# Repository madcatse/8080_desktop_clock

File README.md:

# i8080 homebrew digital clock/weather station (fork)

## Русский

Этот репозиторий — форк проекта **"i8080 homebrew digital clock/weather station"** автора **Tronix286**: 
<https://github.com/Tronix286/i8080_clock>.

Моя цель — сделать часы более презентабельными и свести к минимуму использование SMD‑компонентов (с таким процессором использовать их «не комильфо»). Я очень благодарен автору за схему и само устройство — без этой базы не получилось бы так быстро продвинуться.

Ключевое отличие от исходного проекта: в этом форке сделан упор на внешний вид и на максимально сквозной/выводной монтаж, поэтому плата и компоновка ориентированы на более «классическое» исполнение и удобство сборки, при сохранении общей архитектуры.

### Что внутри

**Аппаратная часть**
- Плата i8080‑совместимого компьютера с тактированием, шиной, ПЗУ/ОЗУ и часами реального времени.
- Внешние устройства: TFT‑дисплей, датчики по I2C и 1‑Wire, кнопки.

**Проект в KiCad**
- Полный проект схемы и платы находится в каталоге `hardware/`.

### ПО

Сборка прошивки описана в каталоге `software/` (используется z88dk и собственная цель `clock80`).

### 3D

Трехмерная модель собранных часов, а также модели треугольные ножки для 3d-печати.

---

## English

This repository is a fork of **"i8080 homebrew digital clock/weather station"** by **Tronix286**: 
<https://github.com/Tronix286/i8080_clock>.

My goal is to make the clock look more presentable and to minimize the number of SMD parts (with a CPU like this, using SMD feels out of place). I am very grateful to the author for the schematic and the original device — it provided the essential foundation for this work.

Key difference vs the original project: this fork focuses on the physical appearance and on keeping the design as through‑hole as possible. The PCB layout and mechanical decisions are tailored to a more classic, build‑friendly presentation while preserving the overall architecture.

### What’s inside

**Hardware**
- i8080‑compatible system board with clocking, bus, ROM/RAM, and real‑time clock.
- External devices: TFT display, I2C and 1‑Wire sensors, and buttons.

**KiCad project**
- Full schematic and PCB project live under `hardware/`.

### Software

Firmware build instructions and sources are in `software/` (z88dk with a custom `clock80` target).

### 3D

3D model of assembled clock, and models of triangle stands for 3d printing.

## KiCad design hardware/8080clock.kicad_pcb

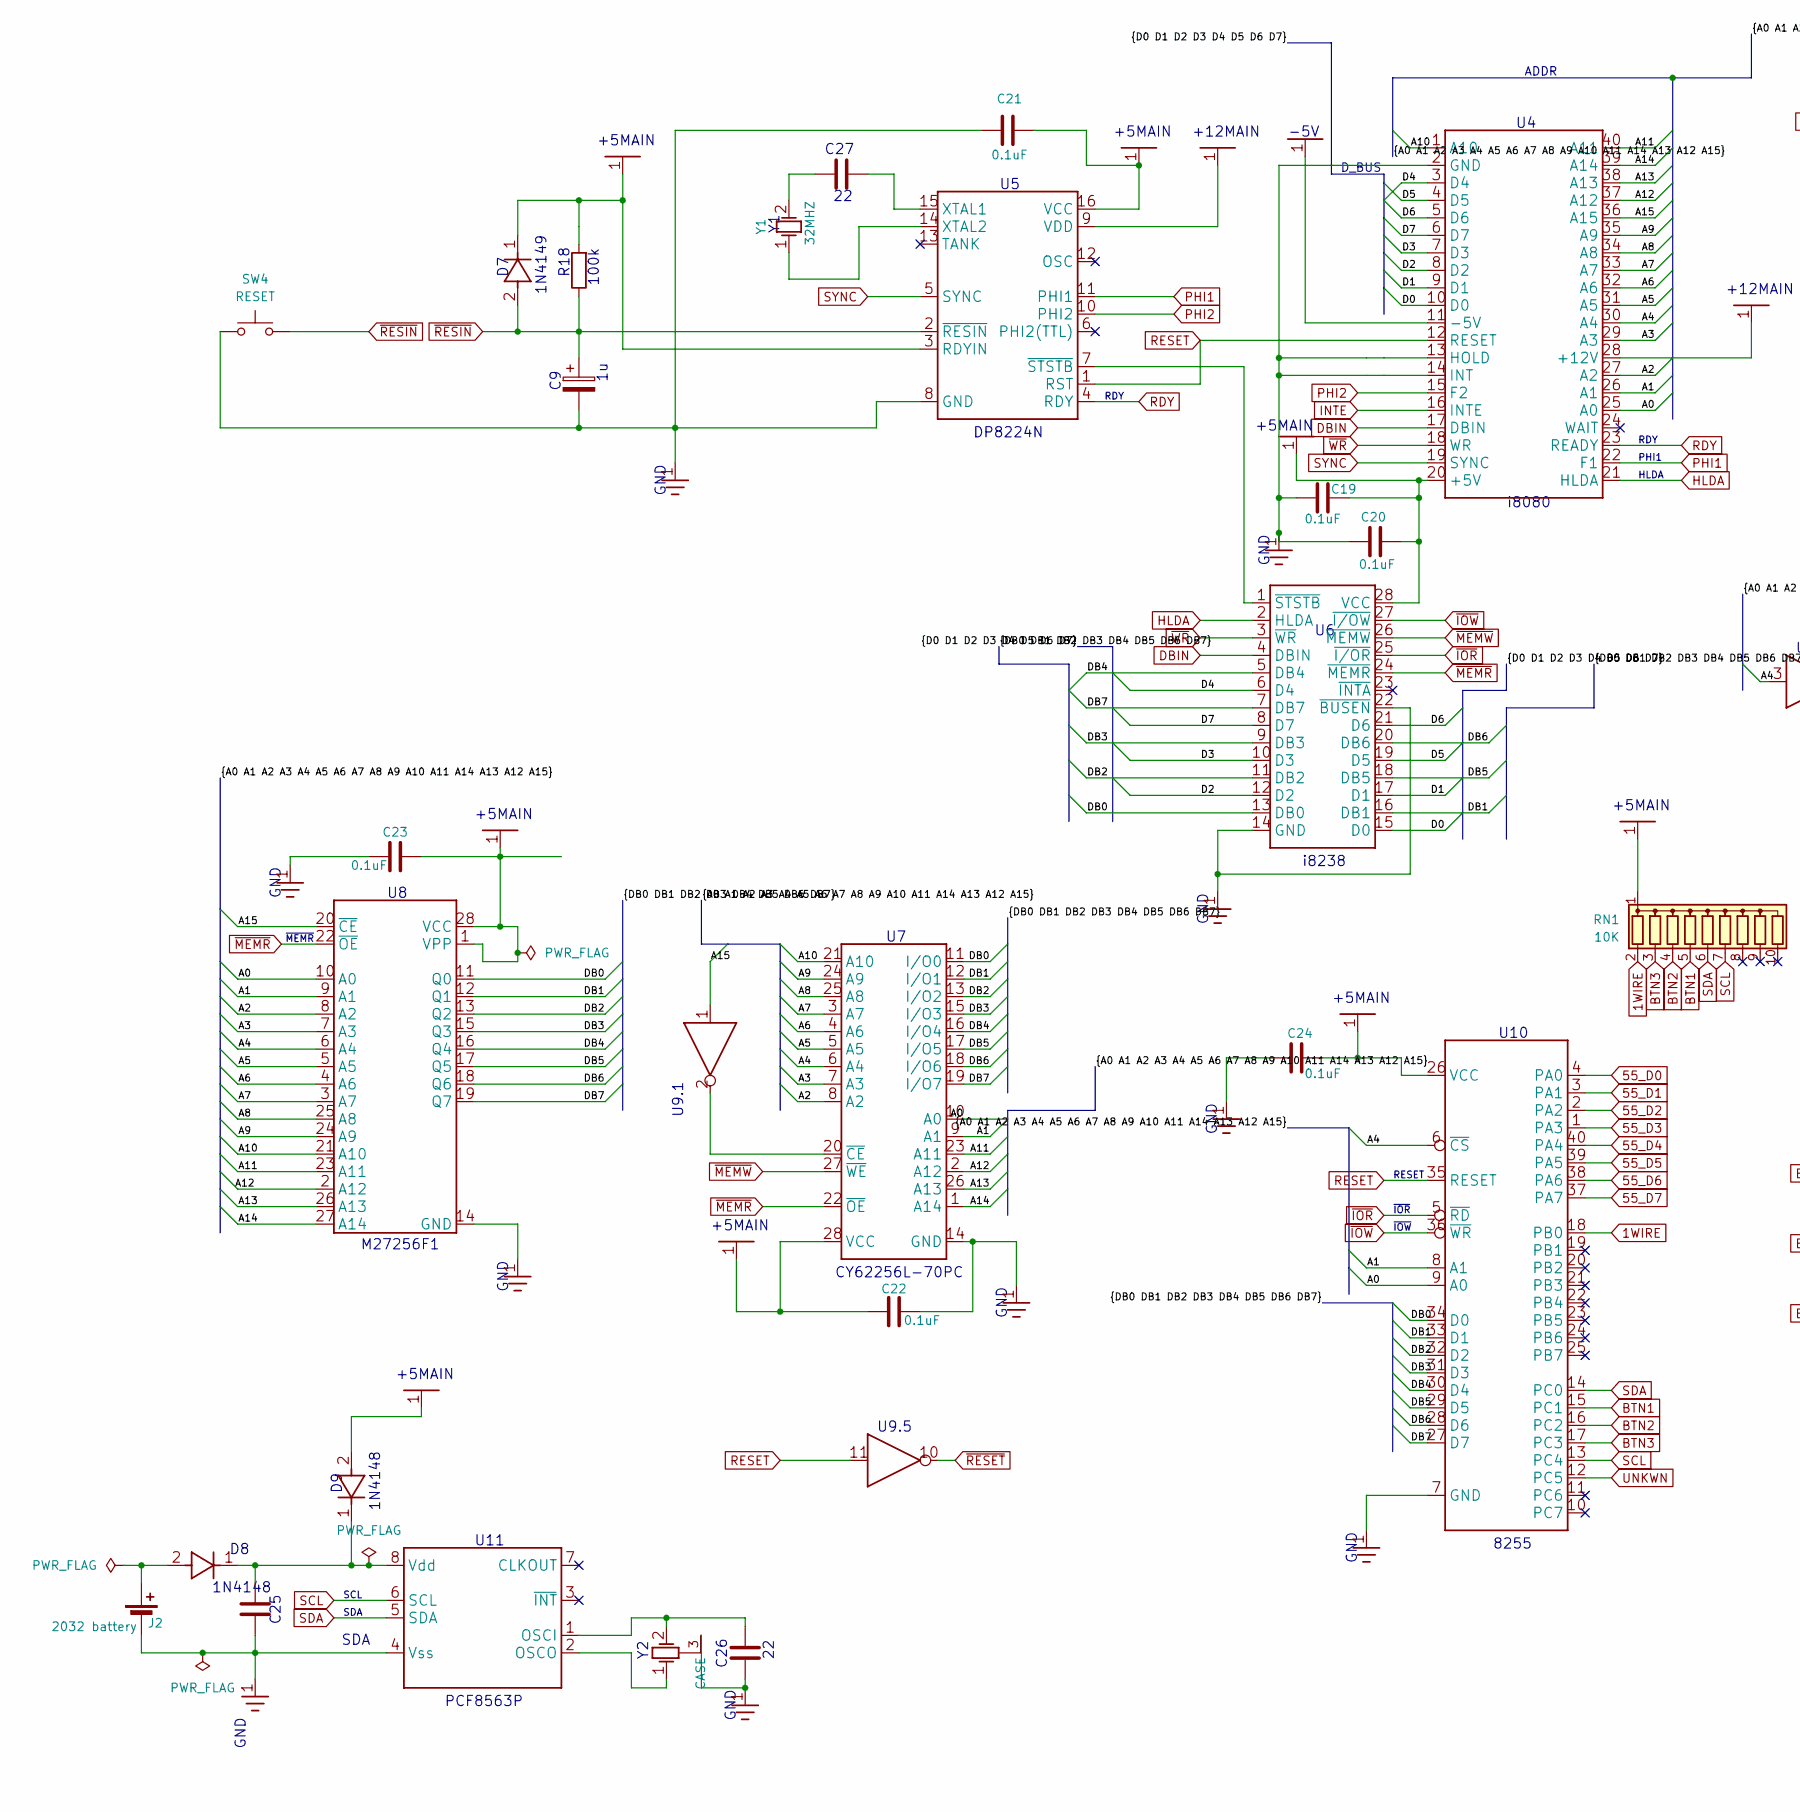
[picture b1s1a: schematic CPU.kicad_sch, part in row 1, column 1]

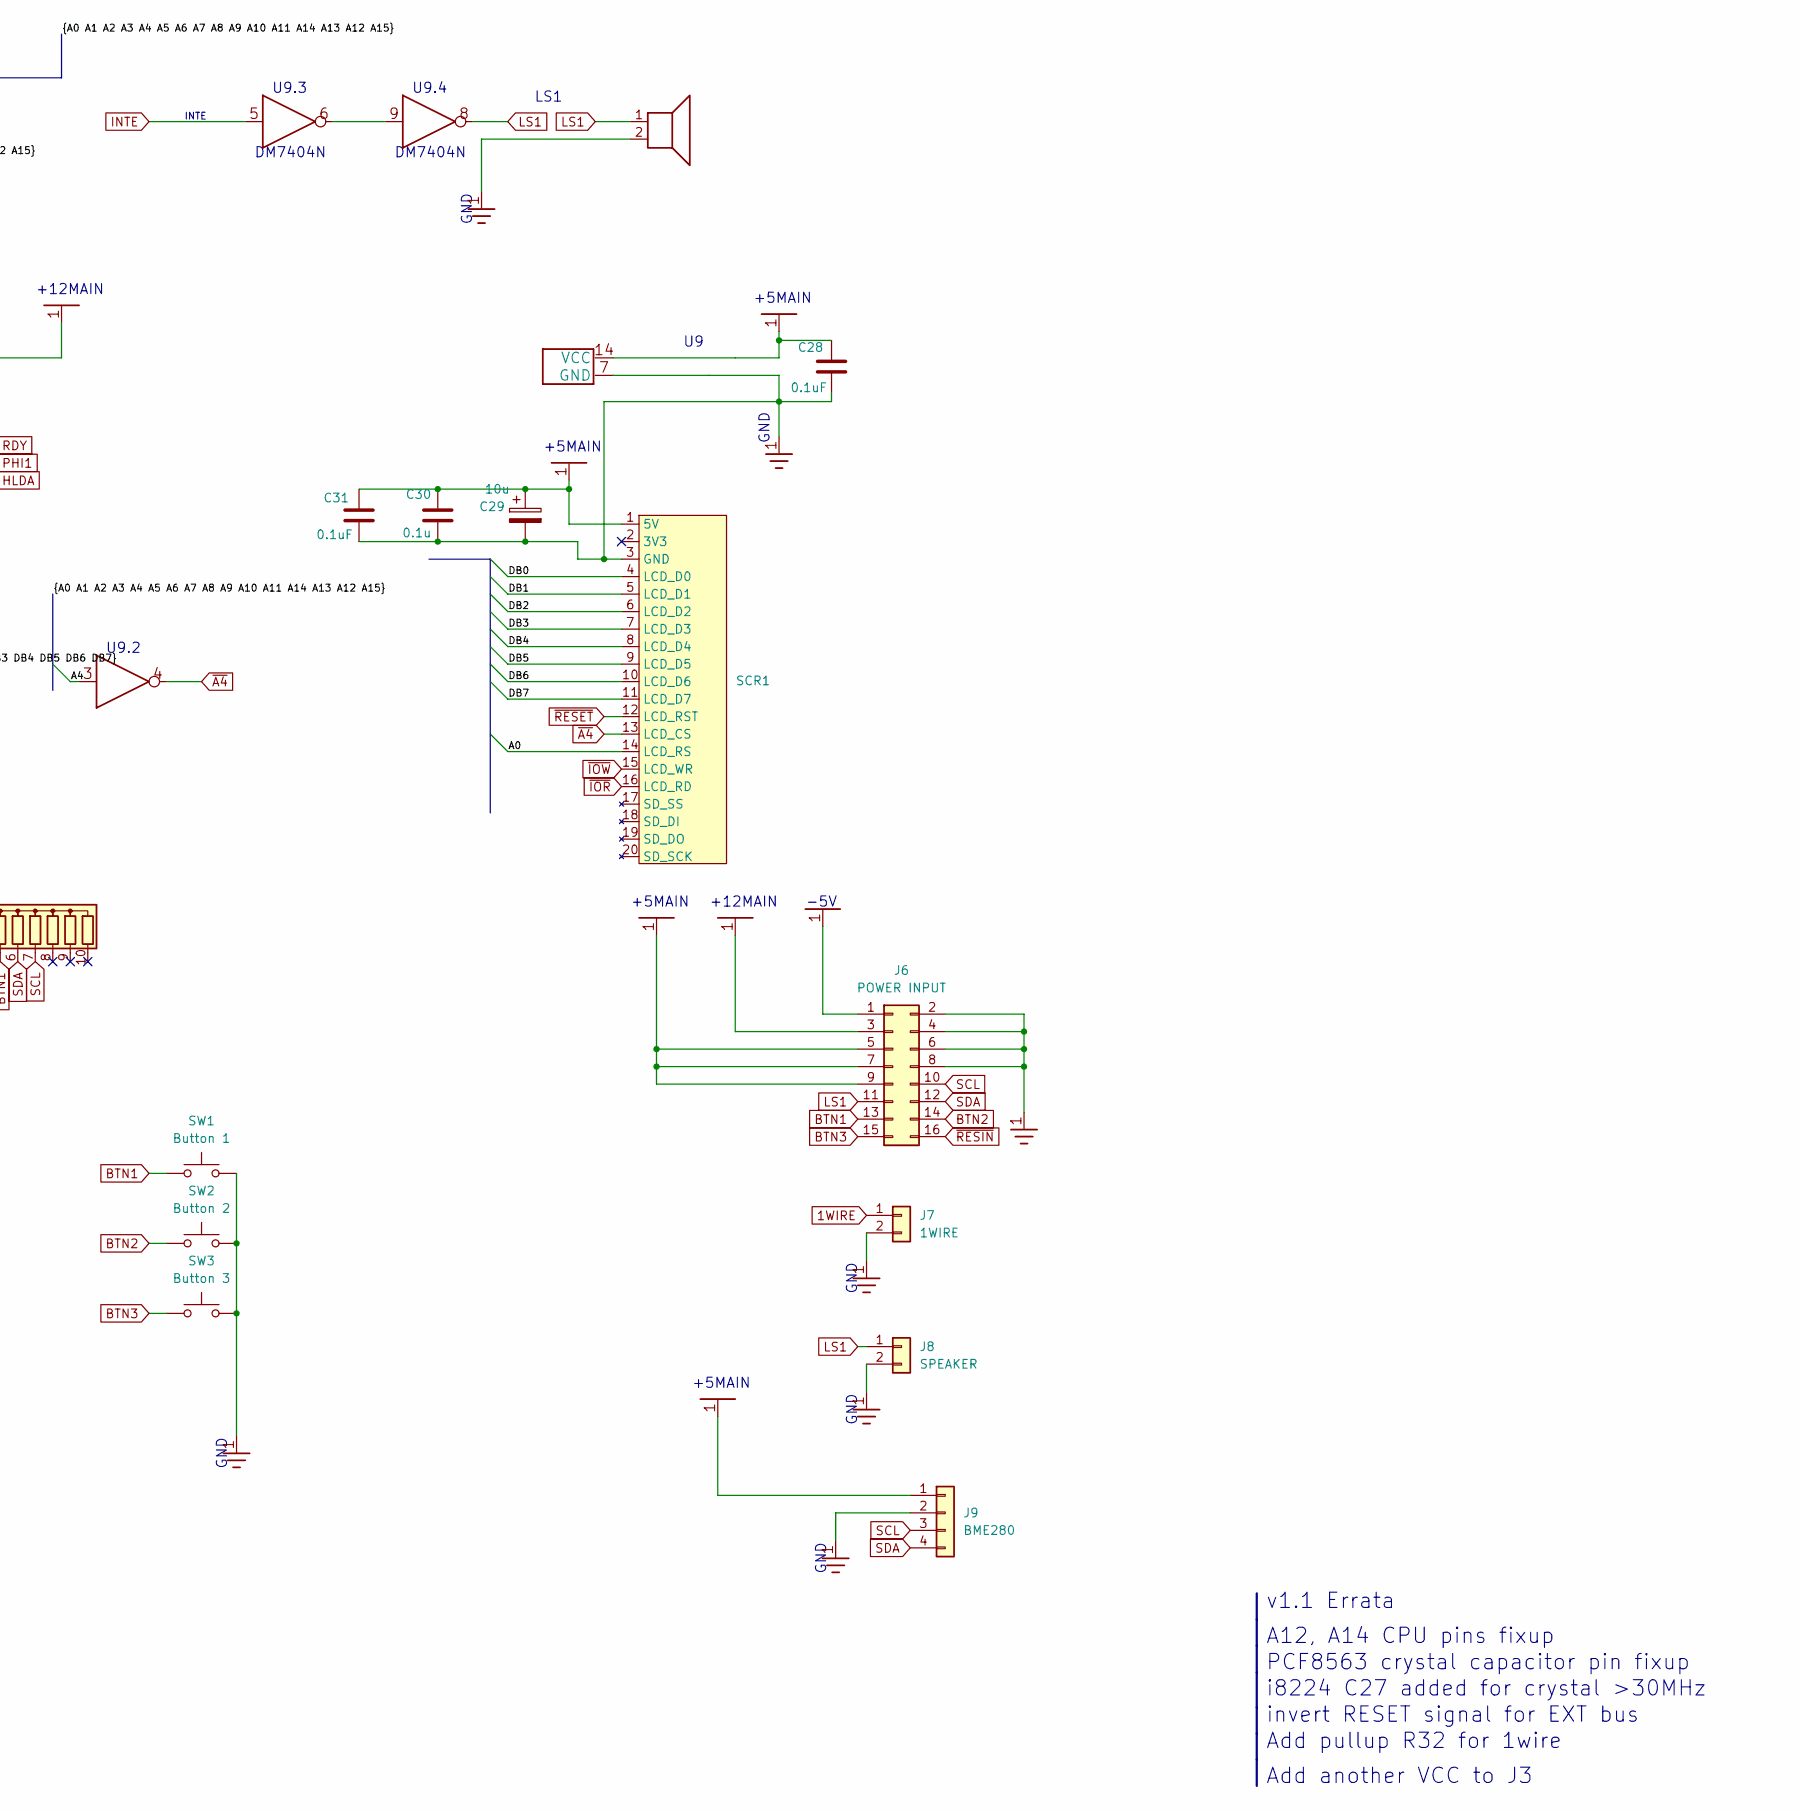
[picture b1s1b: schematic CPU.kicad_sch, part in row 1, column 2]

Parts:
C9: 1u; CP_Radial_D6.3mm_P2.50mm
C19, C20, C21, C22, C23, C24, C28, C31: 0.1uF; C_Disc_D7.0mm_W2.5mm_P5.00mm
C25: 0.01uF; C_Disc_D7.0mm_W2.5mm_P5.00mm
C26, C27: 22pF; C_Disc_D7.0mm_W2.5mm_P5.00mm
C29: 10u; CP_Radial_D5.0mm_P2.50mm
C30: 0.1u; C_Disc_D7.0mm_W2.5mm_P5.00mm
D7, D8, D9: 1N4148; D_DO-35_SOD27_P10.16mm_Horizontal
J2: 2032 battery; BatteryHolder_MYOUNG_BS-07-A1BJ001_CR2032
J6: POWER INPUT; IDC-Header_2x08_P2.54mm_Vertical
J7: 1WIRE; PinHeader_1x02_P2.54mm_Vertical
J8: SPEAKER; PinHeader_1x02_P2.54mm_Vertical
J9: BME280; BME280_sensor
LS1: AI-1223-TWT-5V-R; Buzzer_12x9.5RM7.6
R18: 100k; R_Axial_DIN0207_L6.3mm_D2.5mm_P10.16mm_Horizontal
RN1: 10K; R_Array_SIP10
SCR1: SCREEN
SW1: Button 1; SW_PUSH_6mm
SW2: Button 2; SW_PUSH_6mm
SW3: Button 3; SW_PUSH_6mm
SW4: RESET; SW_PUSH_6mm
U5: Intel 8224 / КР580ГФ24; DIP-16_W7.62mm_Socket_LongPads
U6: Intel 8238 / КР580ВК38; DIP-28_W15.24mm_Socket_LongPads
U7: CY62256L-70PC; DIP-28_W7.62mm_Socket_LongPads
U8: 27C256 / КР573РФ8; DIP-28_W15.24mm_Socket_LongPads
U9: 74LS04 / К555ЛН1; DIP-14_W7.62mm_Socket_LongPads
U10: Intel 8255A / КР580ВВ55А; DIP-40_W15.24mm_Socket_LongPads
U11: PCF8563P; DIP-8_W7.62mm_Socket_LongPads
U12: Intel 8080 / КР580ВМ80; DIP-40_W15.24mm_Socket_LongPads
Y1: 32MHZ; Crystal_HC49-4H_Vertical
Y2: 32.768; Crystal_DS15_D1.5mm_L5.0mm_Horizontal_1EP_style1

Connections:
1WIRE: J7.1, RN1.2 (R1), U10.18 (PB0)
55_D0: U10.4 (PA0)
55_D1: U10.3 (PA1)
55_D2: U10.2 (PA2)
55_D3: U10.1 (PA3)
55_D4: U10.40 (PA4)
55_D5: U10.39 (PA5)
55_D6: U10.38 (PA6)
55_D7: U10.37 (PA7)
+5MAIN: C19.2, C20.2, C21.1, C22.1, C23.2, C24.2, C28.2, C29.1, C30.2, C31.2, D7.1 (K), D9.2 (A), J6.5, J6.7, J6.9, J9.1, R18.2, RN1.1 (common), SCR1.1 (5V), U5.3 (RDYIN), U5.16 (VCC), U6.28 (VCC), U7.28 (VCC), U8.1 (VPP), U8.28 (VCC), U9.14 (VCC), U10.26 (VCC), U12.20 (+5V); also elsewhere on the board
+12MAIN: J6.3, U5.9 (VDD), U12.28 (+12V); also elsewhere on the board
-5V: J6.1, U12.11 (-5V); also elsewhere on the board
/CPU/A0: SCR1.14 (LCD_RS), U7.10 (A0), U8.10 (A0), U10.9 (A0), U12.25 (A0)
/CPU/A1: U7.9 (A1), U8.9 (A1), U10.8 (A1), U12.26 (A1)
/CPU/A2: U7.8 (A2), U8.8 (A2), U12.27 (A2)
/CPU/A3: U7.7 (A3), U8.7 (A3), U12.29 (A3)
/CPU/A4: U7.6 (A4), U8.6 (A4), U9.3 (A), U10.6 (~CS), U12.30 (A4)
/CPU/A5: U7.5 (A5), U8.5 (A5), U12.31 (A5)
/CPU/A6: U7.4 (A6), U8.4 (A6), U12.32 (A6)
/CPU/A7: U7.3 (A7), U8.3 (A7), U12.33 (A7)
/CPU/A8: U7.25 (A8), U8.25 (A8), U12.34 (A8)
/CPU/A9: U7.24 (A9), U8.24 (A9), U12.35 (A9)
/CPU/A10: U7.21 (A10), U8.21 (A10), U12.1 (A10)
/CPU/A11: U7.23 (A11), U8.23 (A11), U12.40 (A11)
/CPU/A12: U7.2 (A12), U8.2 (A12), U12.37 (A12)
/CPU/A13: U7.26 (A13), U8.26 (A13), U12.38 (A13)
/CPU/A14: U7.1 (A14), U8.27 (A14), U12.39 (A14)
/CPU/A15: U8.20 (~CE), U9.1 (A), U12.36 (A15)
/CPU/D0: U6.15 (D0), U12.10 (D0)
/CPU/D1: U6.17 (D1), U12.9 (D1)
/CPU/D2: U6.12 (D2), U12.8 (D2)
/CPU/D3: U6.10 (D3), U12.7 (D3)
/CPU/D4: U6.6 (D4), U12.3 (D4)
/CPU/D5: U6.19 (D5), U12.4 (D5)
/CPU/D6: U6.21 (D6), U12.5 (D6)
/CPU/D7: U6.8 (D7), U12.6 (D7)
/CPU/DB0: SCR1.4 (LCD_D0), U6.13 (DB0), U7.11 (I/O0), U8.11 (Q0), U10.34 (D0)
/CPU/DB1: SCR1.5 (LCD_D1), U6.16 (DB1), U7.12 (I/O1), U8.12 (Q1), U10.33 (D1)
/CPU/DB2: SCR1.6 (LCD_D2), U6.11 (DB2), U7.13 (I/O2), U8.13 (Q2), U10.32 (D2)
/CPU/DB3: SCR1.7 (LCD_D3), U6.9 (DB3), U7.15 (I/O3), U8.15 (Q3), U10.31 (D3)
/CPU/DB4: SCR1.8 (LCD_D4), U6.5 (DB4), U7.16 (I/O4), U8.16 (Q4), U10.30 (D4)
/CPU/DB5: SCR1.9 (LCD_D5), U6.18 (DB5), U7.17 (I/O5), U8.17 (Q5), U10.29 (D5)
/CPU/DB6: SCR1.10 (LCD_D6), U6.20 (DB6), U7.18 (I/O6), U8.18 (Q6), U10.28 (D6)
/CPU/DB7: SCR1.11 (LCD_D7), U6.7 (DB7), U7.19 (I/O7), U8.19 (Q7), U10.27 (D7)
BTN1: J6.13, RN1.5 (R4), SW1.2, U10.15 (PC1); also elsewhere on the board
BTN2: J6.14, RN1.4 (R3), SW2.2, U10.16 (PC2); also elsewhere on the board
BTN3: J6.15, RN1.3 (R2), SW3.2, U10.17 (PC3); also elsewhere on the board
DBIN: U6.4 (DBIN), U12.17 (DBIN)
GND: C9.2, C19.1, C20.1, C21.2, C22.2, C23.1, C24.1, C25.1, C26.2, C28.1, C29.2, C30.1, C31.1, J2.2 (-), J6.2, J6.4, J6.6, J6.8, J7.2, J8.2, J9.2, LS1.2, SCR1.3 (GND), SW1.1, SW2.1, SW3.1, SW4.2, U5.8 (GND), U6.14 (GND), U6.22 (~BUSEN), U7.14 (GND), U8.14 (GND), U9.7 (GND), U10.7 (GND), U11.4 (Vss), U12.2 (GND), U12.13 (HOLD), U12.14 (INT), Y2.3 (CASE); also elsewhere on the board
HLDA: U6.2 (HLDA), U12.21 (HLDA)
INTE: U9.5 (A), U12.16 (INTE)
LS1: J6.11, J8.1, LS1.1, U9.8 (Y); also elsewhere on the board
unnamed: D8.2 (A), J2.1 (+)
unnamed: C25.2, D8.1 (K), D9.1 (K), U11.8 (Vdd)
unnamed: C27.2, U5.15 (XTAL1)
unnamed: U5.14 (XTAL2), Y1.1 (OSC1)
unnamed: U5.7 (~STSTB), U6.1 (~STSTB)
unnamed: U7.20 (~CE), U9.2 (Y)
unnamed: U9.6 (Y), U9.9 (A)
unnamed: C26.1, U11.1 (OSCI), Y2.2 (OSC2)
unnamed: U11.2 (OSCO), Y2.1 (OSC1)
unnamed: C27.1, Y1.2 (OSC2)
PHI1: U5.11 (PHI1), U12.22 (F1)
PHI2: U5.10 (PHI2), U12.15 (F2)
RDY: U5.4 (RDY), U12.23 (READY)
RESET: U5.1 (RST), U9.11 (A), U10.35 (RESET), U12.12 (RESET)
SCL: J6.10, J9.3, RN1.7 (R6), U10.13 (PC4), U11.6 (SCL); also elsewhere on the board
SDA: J6.12, J9.4, RN1.6 (R5), U10.14 (PC0), U11.5 (SDA); also elsewhere on the board
SYNC: U5.5 (SYNC), U12.19 (SYNC)
UNKWN: U10.12 (PC5)
~A4: SCR1.13 (LCD_CS), U9.4 (Y)
~IOR: SCR1.16 (LCD_RD), U6.25 (~I/OR), U10.5 (~RD)
~IOW: SCR1.15 (LCD_WR), U6.27 (~I/OW), U10.36 (~WR)
~MEMR: U6.24 (~MEMR), U7.22 (~OE), U8.22 (~OE)
~MEMW: U6.26 (~MEMW), U7.27 (~WE)
~RESET: SCR1.12 (LCD_RST), U9.10 (Y)
~RESIN: C9.1, D7.2 (A), J6.16, R18.1, SW4.1, U5.2 (~RESIN); also elsewhere on the board
~WR: U6.3 (~WR), U12.18 (WR)

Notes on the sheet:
GND
-5V
U9.2
LS1
U9.3
1N4148
R18
+5MAIN
PCF8563 crystal capacitor pin fixup
SDA
A12, A14 CPU pins fixup
D_BUS
U9.1
~{IOR}
+12MAIN
Add another VCC to J3
RDY
~{IOW}
U9.4
100k
DM7404N
C27
U10
C25
C26
CY62256L-70PC
PHI1
v1.1 Errata
~{MEMR}
U9.5
invert RESET signal for EXT bus
PCF8563P
INTE
RESET
i8080
SCL
HLDA
Add pullup R32 for 1wire
i8224 C27 added for crystal >30MHz
M27256F1

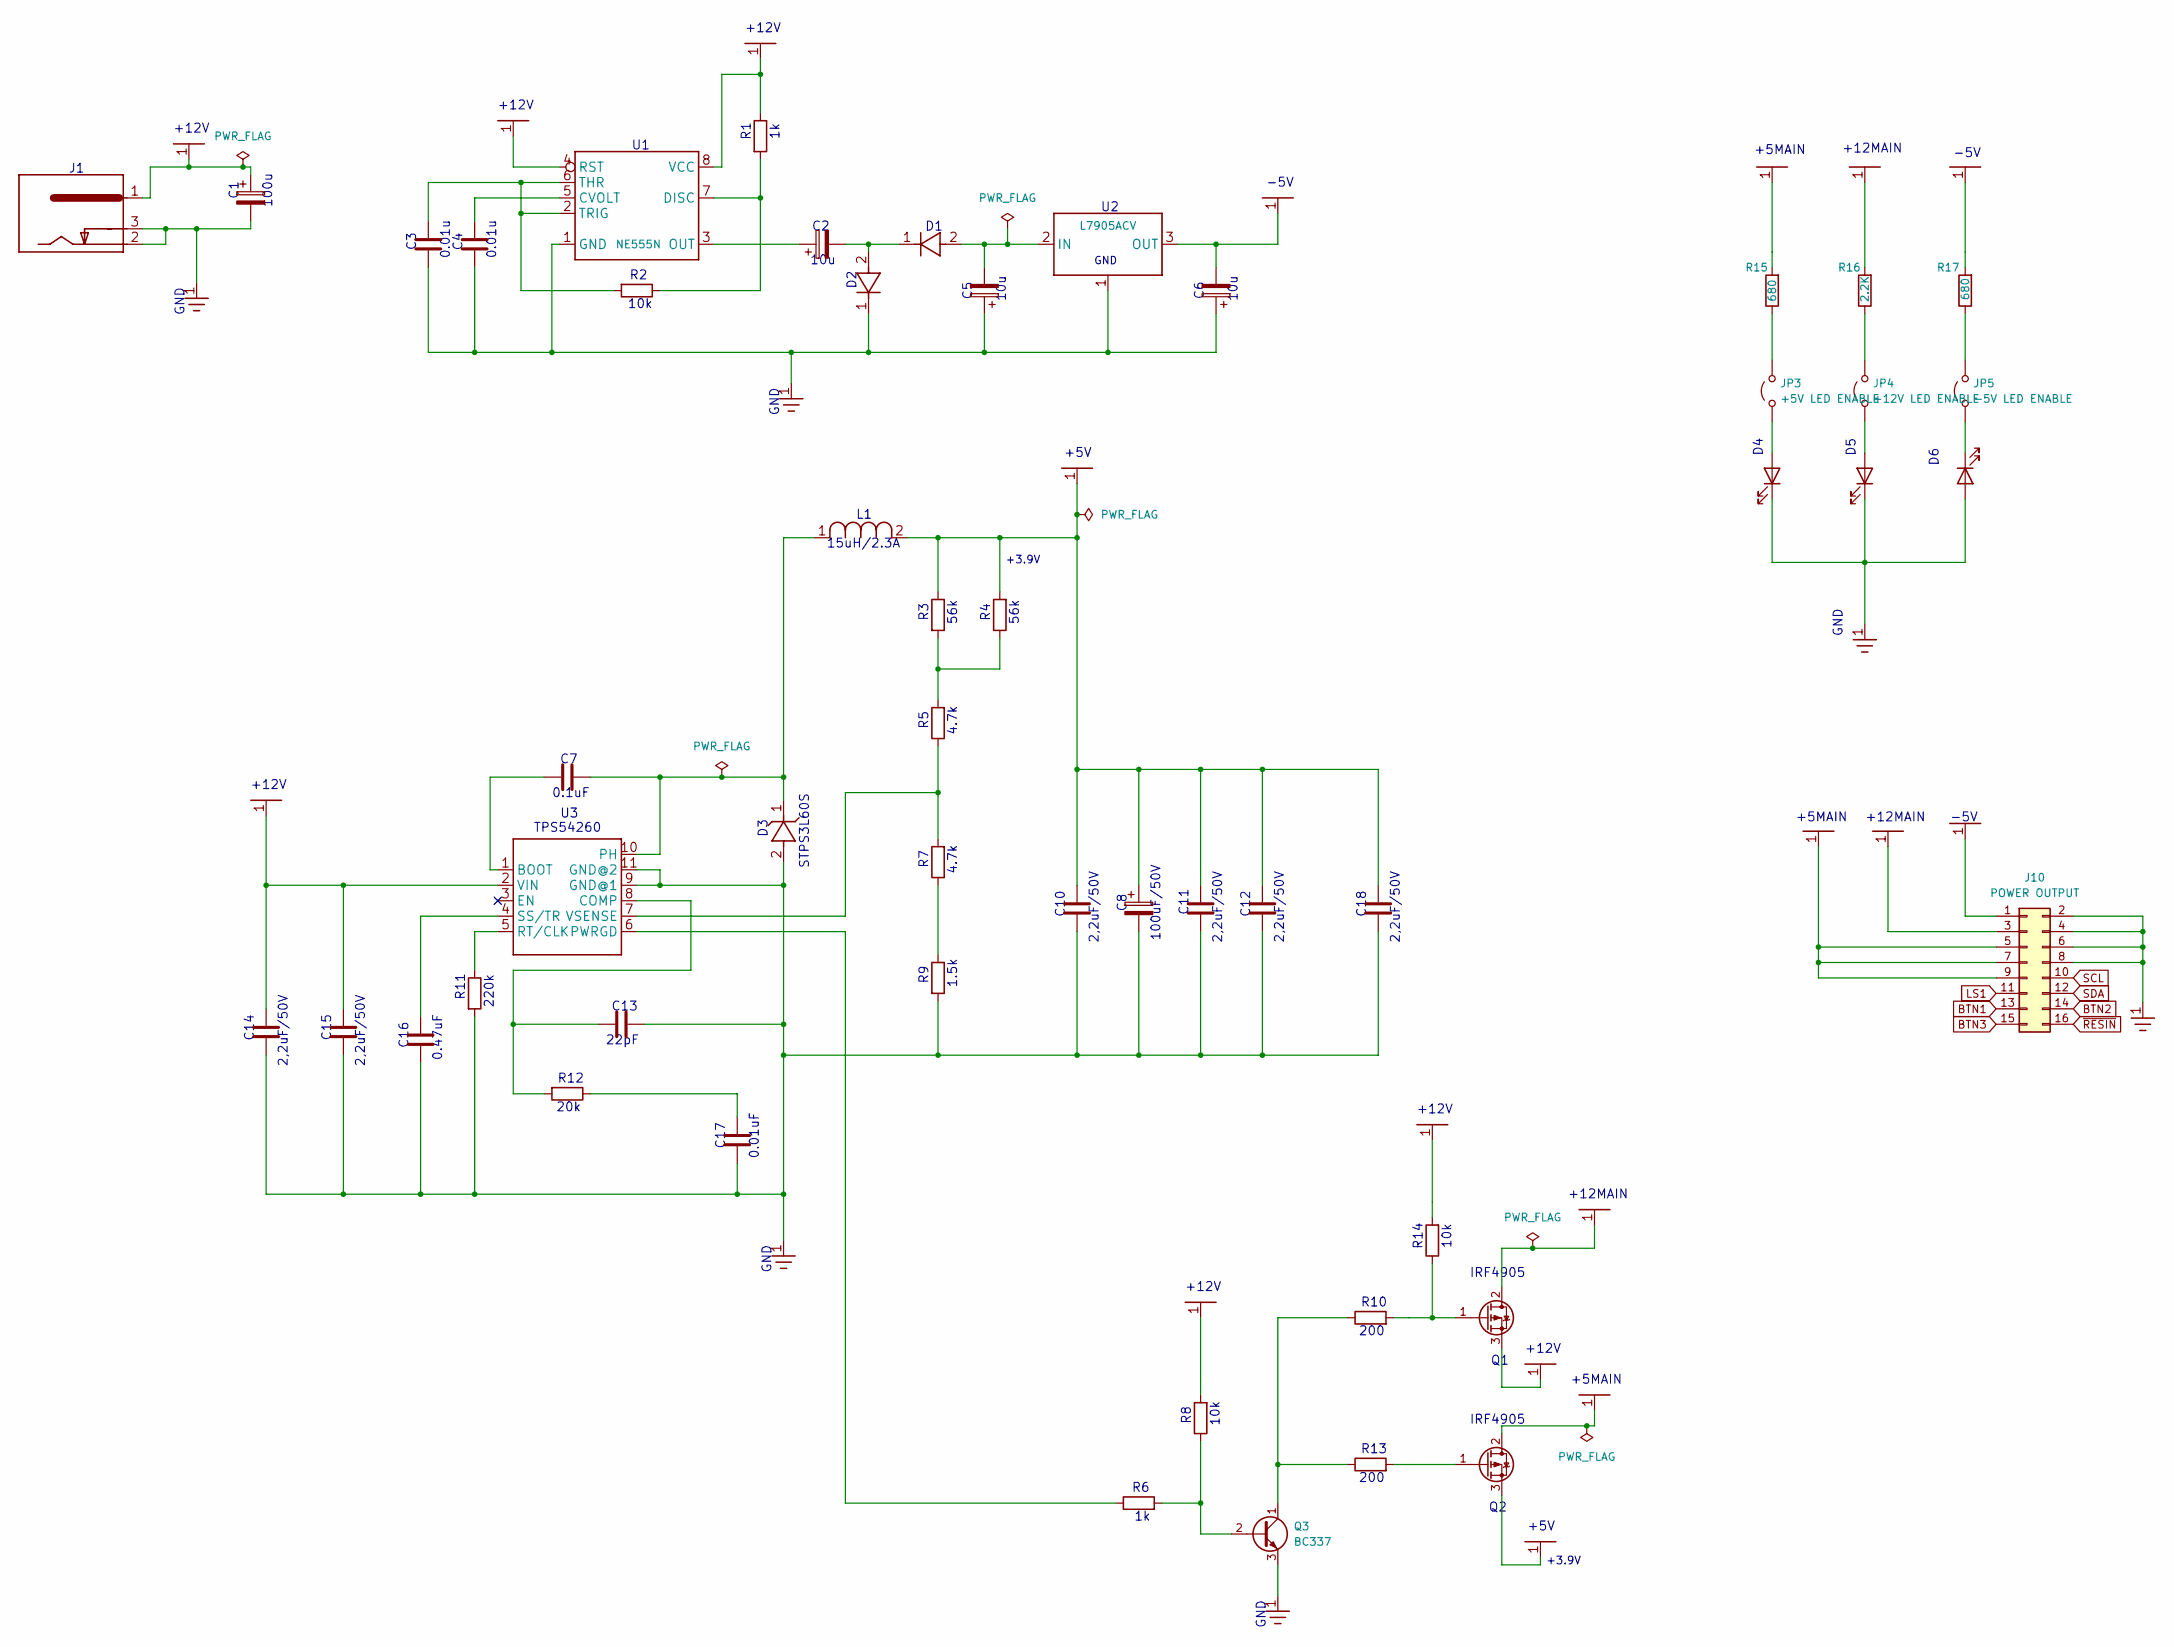
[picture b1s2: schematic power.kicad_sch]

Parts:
C1: 100uF 25V; CP_Radial_D8.0mm_P5.00mm
C2, C5: 10u; CP_Radial_D5.0mm_P2.50mm
C3, C4: 0.01u; C_Disc_D7.0mm_W2.5mm_P5.00mm
C6: 10u 16V; CP_Radial_D5.0mm_P2.50mm
C7: 0.1uF; C_Disc_D7.0mm_W2.5mm_P5.00mm
C8: 100uF/50V; CP_Radial_D8.0mm_P3.50mm
C10, C11, C12, C18: 2,2uF; C_1206_3216Metric_Pad1.33x1.80mm_HandSolder
C13: 22pF; C_Disc_D7.0mm_W2.5mm_P5.00mm
C14, C15: 2,2uF/50V; C_1206_3216Metric_Pad1.33x1.80mm_HandSolder
C16: 0.47uF; C_Disc_D7.0mm_W2.5mm_P5.00mm
C17: 0.01uF; C_Disc_D7.0mm_W2.5mm_P5.00mm
D1, D2: 1N4148; D_DO-35_SOD27_P10.16mm_Horizontal
D3: STPS3L60S; D_SMC_Handsoldering
D4: +5V; LED_D5.0mm
D5: +12V; LED_D5.0mm
D6: -5V; LED_D5.0mm
J1: 4840-2201; BarrelJack_GCT_DCJ200-10-A_Horizontal
J10: POWER OUTPUT; IDC-Header_2x08_P2.54mm_Vertical
JP3: +5V LED ENABLE; TestPoint_2Pads_Pitch2.54mm_Drill0.8mm
JP4: +12V LED ENABLE; TestPoint_2Pads_Pitch2.54mm_Drill0.8mm
JP5: -5V LED ENABLE; TestPoint_2Pads_Pitch2.54mm_Drill0.8mm
L1: 15uH/2.3A; CDRH8D43NP-100NC
Q1, Q2: IRF4905; TO-220-3_Horizontal_TabDown
Q3: BC337; TO-92L_Inline
R1, R6: 1k; R_Axial_DIN0207_L6.3mm_D2.5mm_P10.16mm_Horizontal
R2, R8, R14: 10k; R_Axial_DIN0207_L6.3mm_D2.5mm_P10.16mm_Horizontal
R3, R4: 56k; R_Axial_DIN0207_L6.3mm_D2.5mm_P10.16mm_Horizontal
R5, R7: 4.7k; R_Axial_DIN0207_L6.3mm_D2.5mm_P10.16mm_Horizontal
R9: 1.5k; R_Axial_DIN0207_L6.3mm_D2.5mm_P10.16mm_Horizontal
R10, R13: 200; R_Axial_DIN0207_L6.3mm_D2.5mm_P10.16mm_Horizontal
R11: 220k; R_Axial_DIN0207_L6.3mm_D2.5mm_P10.16mm_Horizontal
R12: 20k; R_Axial_DIN0207_L6.3mm_D2.5mm_P10.16mm_Horizontal
R15, R17: 680; R_Axial_DIN0207_L6.3mm_D2.5mm_P10.16mm_Horizontal
R16: 2.2K; R_Axial_DIN0207_L6.3mm_D2.5mm_P10.16mm_Horizontal
U1: NE555N; DIP-8_W7.62mm_Socket_LongPads
U2: L7905ACV; TO-220-3_Horizontal_TabDown
U3: TPS54260; HVSSOP-10-1EP_3x3mm_P0.5mm_EP1.57x1.88mm

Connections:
+5MAIN: J10.5, J10.7, J10.9, Q2.2 (D), R15.2; also elsewhere on the board
+5V: C8.1, C10.1, C11.1, C12.1, C18.1, L1.2, Q2.3 (S), R3.1, R4.2
+12MAIN: J10.3, Q1.2 (D), R16.2; also elsewhere on the board
+12V: C1.1, C14.1, C15.1, J1.1, Q1.3 (S), R1.1, R8.2, R14.2, U1.4 (RST), U1.8 (VCC), U3.2 (VIN)
-5V: C6.2, J10.1, R17.2, U2.3 (OUT); also elsewhere on the board
BTN1: J10.13; also elsewhere on the board
BTN2: J10.14; also elsewhere on the board
BTN3: J10.15; also elsewhere on the board
GND: C1.2, C3.1, C4.1, C5.1, C6.1, C8.2, C10.2, C11.2, C12.2, C13.2, C14.2, C15.2, C16.2, C17.2, C18.2, D2.1 (K), D3.2 (A), D4.1 (K), D5.1 (K), D6.2 (A), J1.2, J1.3, J10.2, J10.4, J10.6, J10.8, Q3.3 (E), R9.2, R11.2, U1.1 (GND), U2.1 (GND), U3.9 (GND@1), U3.11 (GND@2); also elsewhere on the board
LS1: J10.11; also elsewhere on the board
unnamed: C17.1, R12.1
unnamed: C5.2, D1.2 (A), U2.2 (IN)
unnamed: C2.2, D1.1 (K), D2.2 (A)
unnamed: C7.2, D3.1 (K), L1.1, U3.10 (PH)
unnamed: D4.2 (A), JP3.1 (A)
unnamed: D5.2 (A), JP4.1 (A)
unnamed: D6.1 (K), JP5.1 (A)
unnamed: JP3.2 (B), R15.1
unnamed: JP4.2 (B), R16.1
unnamed: JP5.2 (B), R17.1
unnamed: Q1.1 (G), R10.2, R14.1
unnamed: Q2.1 (G), R13.2
unnamed: Q3.2 (B), R6.2, R8.1
unnamed: Q3.1 (C), R10.1, R13.1
unnamed: R3.2, R4.1, R5.2
unnamed: R7.1, R9.1
unnamed: C4.2, U1.5 (CVOLT)
unnamed: R1.2, R2.1, U1.7 (DISC)
unnamed: C2.1, U1.3 (OUT)
unnamed: C3.2, R2.2, U1.2 (TRIG), U1.6 (THR)
unnamed: C7.1, U3.1 (BOOT)
unnamed: C13.1, R12.2, U3.8 (COMP)
unnamed: R6.1, U3.6 (PWRGD)
unnamed: R11.1, U3.5 (RT/CLK)
unnamed: C16.1, U3.4 (SS/TR)
unnamed: R5.1, R7.2, U3.7 (VSENSE)
SCL: J10.10; also elsewhere on the board
SDA: J10.12; also elsewhere on the board
~RESIN: J10.16; also elsewhere on the board

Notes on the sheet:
+12MAIN
4.7k
GND
+5V
220k
10k
10u
C13
+12V
2,2uF/50V
+3.9V
TPS54260
-5V
R11
0.47uF
IRF4905
C17
C12
C11
100uF/50V
0.1uF
200
C16
22pF
R13
R14
56k
+5MAIN
R12
C18
C14
100u
C15
C10
20k
R10
15uH/2.3A
0.01u
0.01uF
STPS3L60S

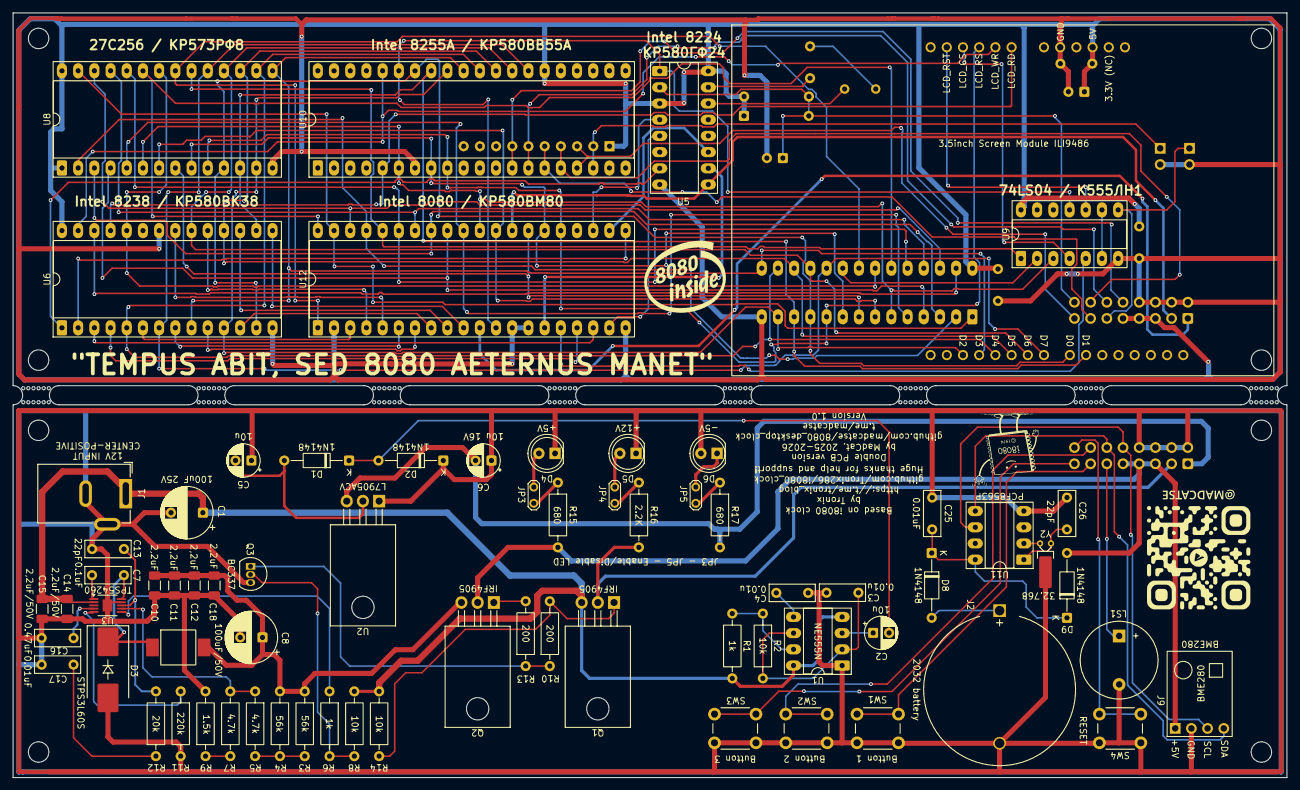
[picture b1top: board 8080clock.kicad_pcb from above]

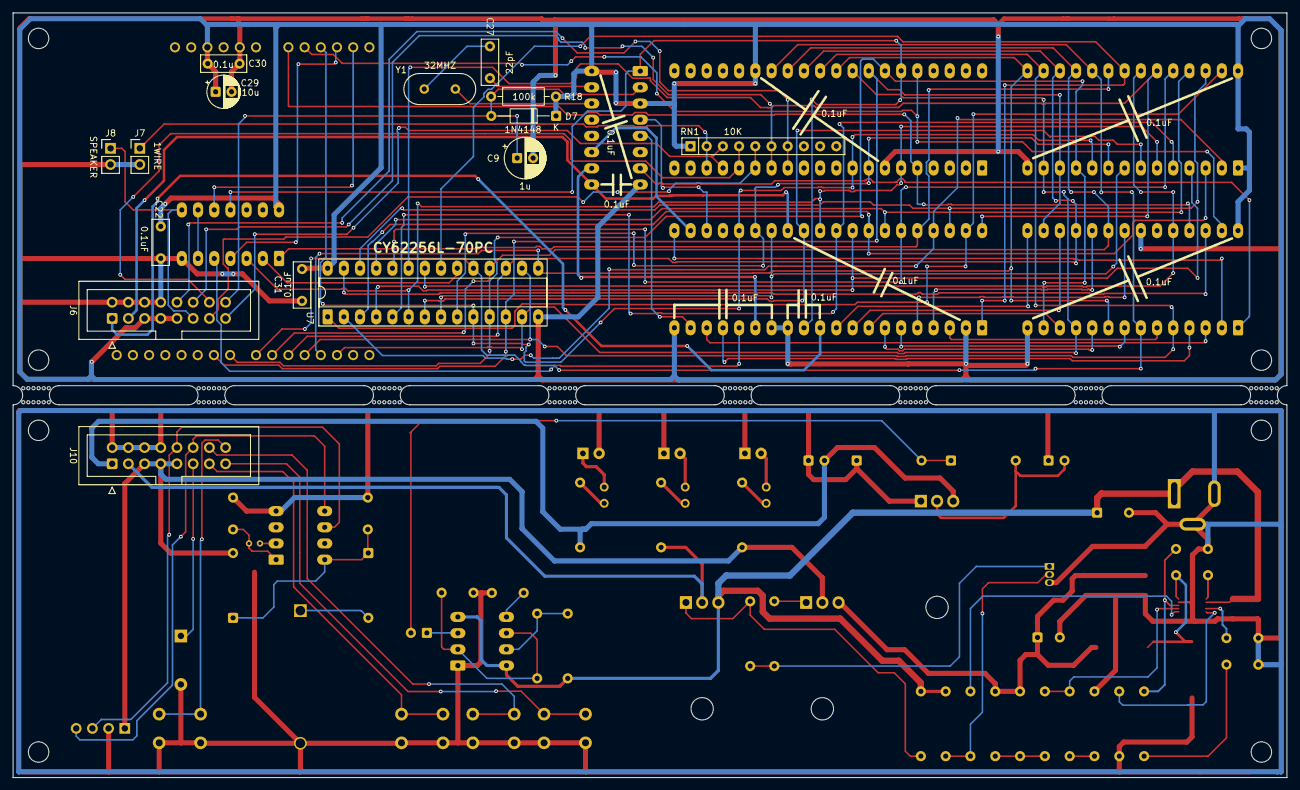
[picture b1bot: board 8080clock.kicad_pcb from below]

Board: 2 copper layers, 199.7 x 119.8 mm, 102 parts (15 on the bottom side), 97 nets.

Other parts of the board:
M1, M2, M3, M4, M5, M6, M7, M8: MountingHole_3.2mm_M3.0
mouse-bite-2.54mm-slot_1, mouse-bite-2.54mm-slot_2, mouse-bite-2.54mm-slot_3, mouse-bite-2.54mm-slot_4, mouse-bite-2.54mm-slot_5, mouse-bite-2.54mm-slot_6, mouse-bite-2.54mm-slot_7, mouse-bite-2.54mm-slot_13: VAL**; mouse_bite

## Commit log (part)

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2026-01-30 Initial Upload
2026-01-30 Rewrite README in Russian and English
2026-01-30 Update README with images and 3D model section
    Added images and 3D model information to README.
2026-02-04 Gerbers
2026-02-17 Small fixes for holes
2026-04-02 Clock Update
